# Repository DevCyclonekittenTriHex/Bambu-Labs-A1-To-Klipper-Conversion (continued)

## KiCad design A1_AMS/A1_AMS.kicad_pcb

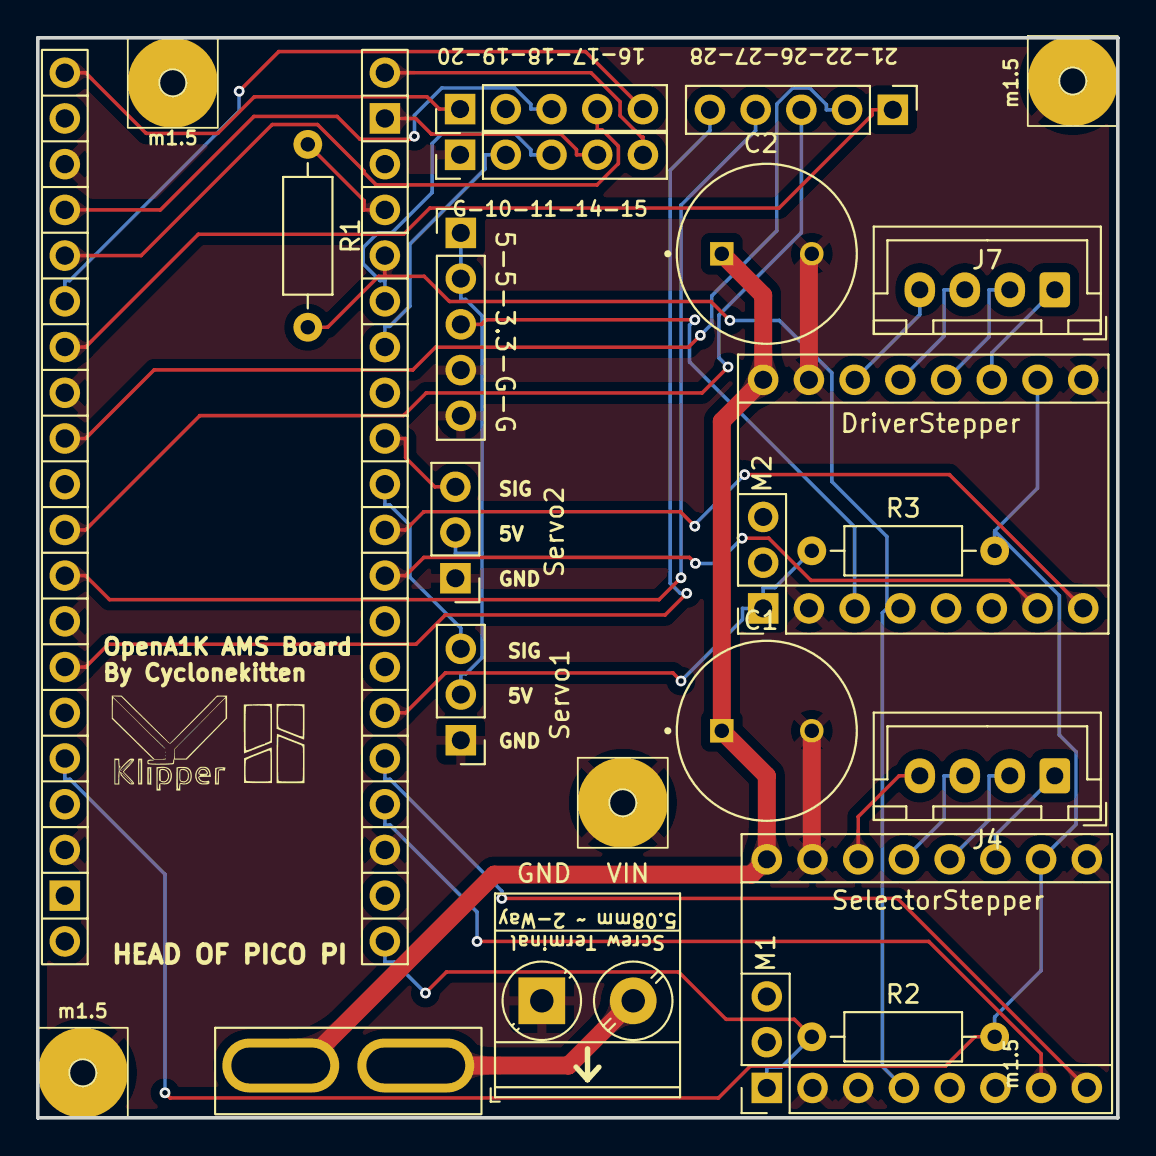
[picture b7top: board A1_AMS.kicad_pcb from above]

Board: 2 copper layers, 60.0 x 60.0 mm, 22 parts (0 on the bottom side), 38 nets.

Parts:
C1, C2: 100uF 63V; Cap63V100UF
F1: M_ATO_FUSE; Updated ATO Mini-Blade_2Post
H1, H3, H5, H6: M1.5; Mountinghole_m1.5
J1: Screw_Terminal_01x02; 1x2 Terminal Block
J2: Servo1; PinHeader_1x03_P2.54mm_Vertical
J3: G-10-11-14-15; PinHeader_1x05_P2.54mm_Vertical
J4, J7: Conn_01x04; JST_XH_B4B-XH-A_1x04_P2.50mm_Vertical
J5: 16-17-18-19-20; PinHeader_1x05_P2.54mm_Vertical
J6: 21-22-26-27-28; PinHeader_1x05_P2.54mm_Vertical
J8: 5-5-3.3-G-G; PinHeader_1x05_P2.54mm_Vertical
J9: Servo2; PinHeader_1x03_P2.54mm_Vertical
M1, M2: StepperMotor; TMC2209 Footprint
R1: 1kΩ; R_Axial_DIN0207_L6.3mm_D2.5mm_P10.16mm_Horizontal
R2, R3: 10kΩ; R_Axial_DIN0207_L6.3mm_D2.5mm_P10.16mm_Horizontal
U1: Pico; Socketed MCU - Pico (No Text)

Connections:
+3V3: M1.10 (VDD), M2.10 (VDD), R2.2, R3.2, U1.36 (3V3)
/3V3: J8.3, M2.3 (MS2)
/5V: J2.2, J8.1, J8.2, J9.2
/DriveMotor/A1: J7.3, M2.13 (A1)
/DriveMotor/A2: J7.4, M2.14 (A2)
/DriveMotor/B1: J7.2, M2.12 (B1)
/DriveMotor/B2: J7.1, M2.11 (B2)
/G10: J3.2, U1.14 (GPIO10)
/G11: J3.3, U1.15 (GPIO11)
/G14: J3.4, U1.19 (GPIO14)
/G15: J3.5, U1.20 (GPIO15)
/G16: J5.1, U1.21 (GPIO16)
/G17: J5.2, U1.22 (GPIO17)
/G18: J5.3, U1.24 (GPIO18)
/G19: J5.4, U1.25 (GPIO19)
/G20: J5.5, U1.26 (GPIO20)
/G21: J6.1, U1.27 (GPIO21)
/G22: J6.2, U1.29 (GPIO22)
/G26: J6.3, U1.31 (GPIO26_ADC0)
/G27: J6.4, U1.32 (GPIO27_ADC1)
/G28: J6.5, U1.34 (GPIO28_ADC2)
/MD_DIR: M2.8 (DIR), U1.10 (GPIO7)
/MD_EN: M2.1 (ENABLE), R3.1, U1.6 (GPIO4)
/MD_STEP: M2.7 (STEP), U1.9 (GPIO6)
/MS_DIR: M1.8 (DIR), U1.5 (GPIO3)
/MS_EN: M1.1 (ENABLE), R2.1, U1.1 (GPIO0)
/MS_STEP: M1.7 (STEP), U1.4 (GPIO2)
/M_UART: M1.4 (PDN1), M2.4 (PDN1), R1.2, U1.16 (GPIO12)
/M_VBUS: C1.1, C2.1, F1.1, M1.16 (VM), M2.16 (VM)
/SV_SIG1: J2.3, U1.11 (GPIO8)
/SV_SIG2: J9.3, U1.12 (GPIO9)
/SelectorMotor/A1: J4.3, M1.13 (A1)
/SelectorMotor/A2: J4.4, M1.14 (A2)
/SelectorMotor/B1: J4.2, M1.12 (B1)
/SelectorMotor/B2: J4.1, M1.11 (B2)
/UART_RX: R1.1, U1.17 (GPIO13)
GND: C1.2, C2.2, H1.1, H3.1, H5.1, H6.1, J1.1, J2.1, J3.1, J8.4, J8.5, J9.1, M1.2 (MS1), M1.3 (MS2), M1.9 (GND), M1.15 (GND), M2.2 (MS1), M2.9 (GND), M2.15 (GND), U1.3 (GND), U1.8 (GND), U1.13 (GND), U1.18 (GND), U1.23 (GND), U1.28 (GND), U1.33 (AGND), U1.38 (GND)
unnamed: F1.2, J1.2

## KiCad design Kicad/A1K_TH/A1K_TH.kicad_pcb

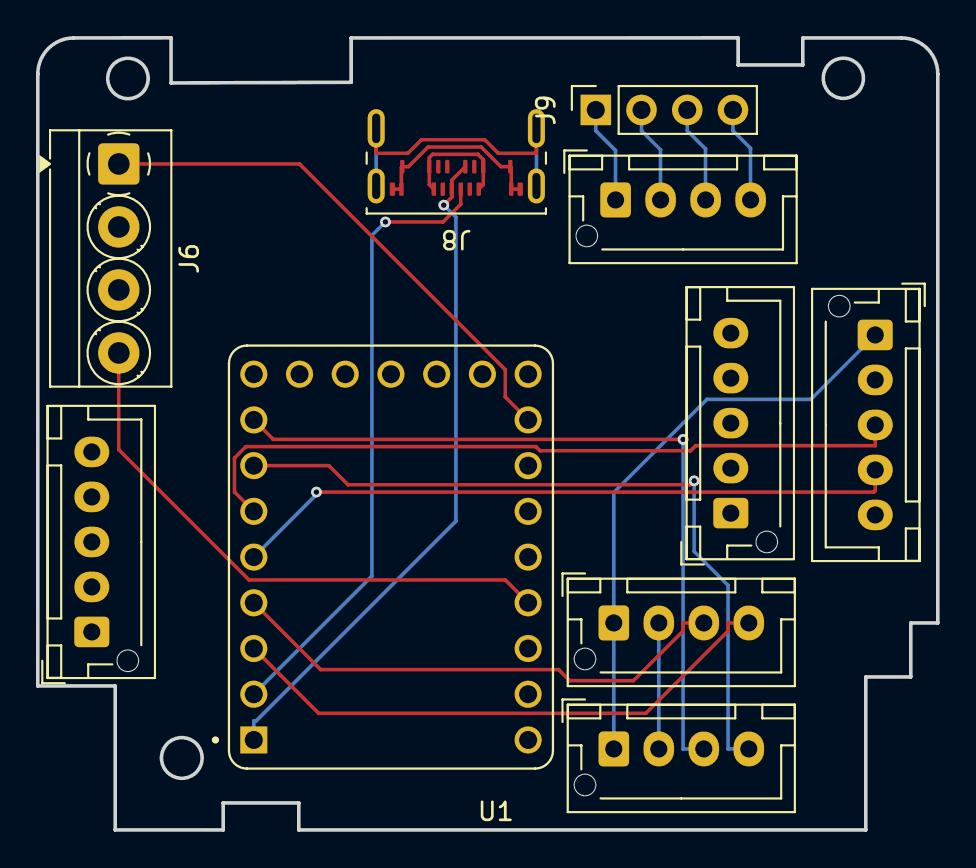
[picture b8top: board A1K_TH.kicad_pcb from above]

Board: 2 copper layers, 50.0 x 44.0 mm, 10 parts (0 on the bottom side), 18 nets.

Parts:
J1: Extruder Motor; JST_XH_B4B-XH-AM_1x04_P2.50mm_Vertical
J2: Part Cooling Fan; JST_XH_B4B-XH-AM_1x04_P2.50mm_Vertical
J3: Extruder Fan; JST_XH_B5B-XH-AM_1x05_P2.50mm_Vertical
J4: Spare Fan; JST_XH_B4B-XH-AM_1x04_P2.50mm_Vertical
J5: Bed Leveling Probe; JST_XH_B5B-XH-AM_1x05_P2.50mm_Vertical
J6: Hotend and Thermister; TerminalBlock_MetzConnect_Type059_RT06304HBWC_1x04_P3.50mm_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
J7: Smart Filament Sensor; JST_XH_B5B-XH-AM_1x05_P2.50mm_Vertical
J8: USB_C_Receptacle; USB_C_Receptacle_Amphenol_124019772112A
J9: E_Motor; PinSocket_1x04_P2.54mm_Vertical
U1: RP2040-ZERO; MODULE_RP2040-ZERO

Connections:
/TH_IO/24V: J2.2, J4.2
/TH_IO/EXF_PWM: J3.4, U1.5 (GP4)
/TH_IO/EXF_TACH: J3.3, U1.6 (GP5)
/TH_IO/EXM_A1: J1.1, J9.1
/TH_IO/EXM_A2: J1.2, J9.2
/TH_IO/EXM_B1: J1.3, J9.3
/TH_IO/EXM_B2: J1.4, J9.4
/TH_IO/GND: J2.1, J3.1, J4.1
/TH_IO/HT_CT: J6.1, U1.16 (GP15)
/TH_IO/PCF_PWM: J2.4, U1.7 (GP6)
/TH_IO/PCF_TACH: J2.3, U1.8 (GP7)
/TH_IO/SPF_PWM: J4.4, U1.3 (GP2)
/TH_IO/SPF_TACH: J4.3, U1.4 (GP3)
/TH_IO/THM_SG: J6.4, U1.20 (GP29)
unnamed: J8.A1 (GND), J8.A12 (GND), J8.B1 (GND), J8.B12 (GND)
unnamed: J8.A4 (VBUS), J8.A9 (VBUS), J8.B4 (VBUS), J8.B9 (VBUS)
unnamed: J8.A7 (D-), J8.B7 (D-), U1.1 (GP0)
unnamed: J8.A6 (D+), J8.B6 (D+), U1.2 (GP1)

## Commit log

2025-02-09 Update README.md
    e
2025-02-09 Update LICENSE
2025-02-09 e
    e
2025-02-11 Create LICENSE
2025-04-02 Create LICENCE
